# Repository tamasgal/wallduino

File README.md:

# WallDuino

Drop-in replacement board for the WallWizard remote-controlled TV wall mount
including PCB, DIY veroboard (stripboard) layouts and an open source firmware
for Arduino compatible microcontrollers.

Manual: [`WallDuino_Manual.pdf`](https://github.com/tamasgal/wallduino/blob/main/docs/WallDuino_Manual.pdf)

## Firmware

Board: Arduino Nano compatible
Dependency: [Arduino-IRRemote v4.5](https://github.com/Arduino-IRremote/Arduino-IRremote)
Code: `firmware/WallDuino`

### Changelog

#### v1.1 - 2026-01-22

- Persistent presets after reboot
- Home button support to "go home"

#### v1.0 - 2026-01-09

Initial release

## PCB

### v1.0 (Rev A) 2026-01-08

First release.

### v1.0 (Rev B) 2026-01-21

- Heat sinking of the L293D improved significantly
- R1, R2 and R3 removed
- Added an additional capacitor to smooth out the position sensor signal from the potentiometer

## DIY Veroboard

The veroboard (stripboard) is Rev A and has a different Arduino pinout, so make sure
to adjust the firmware code.

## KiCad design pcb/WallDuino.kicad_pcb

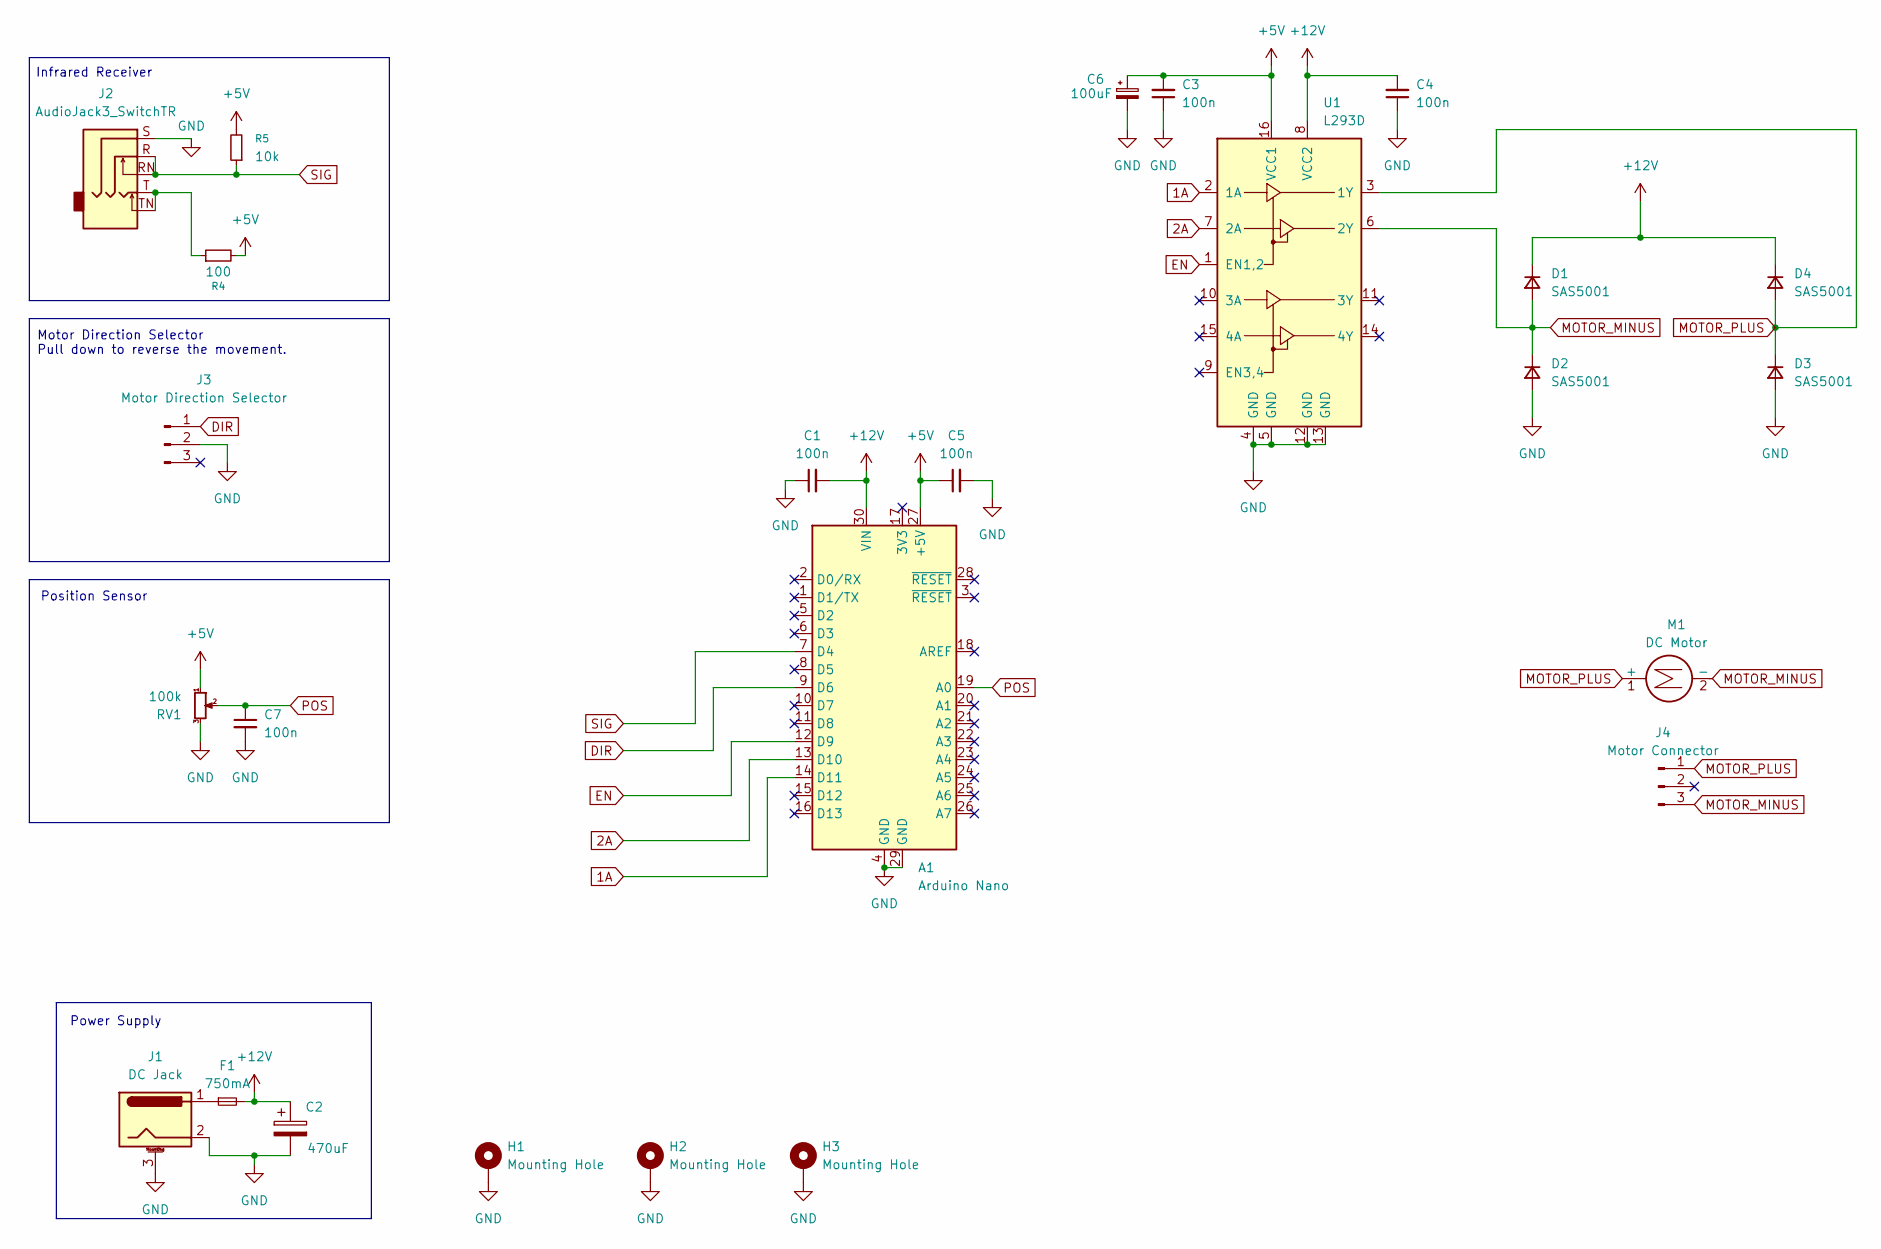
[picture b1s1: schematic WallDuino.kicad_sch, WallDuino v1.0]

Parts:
A1: Arduino Nano; Arduino_Nano
C1, C3, C4, C5, C7: 100n; C_Disc_D3.0mm_W1.6mm_P2.50mm
C2: 470uF; CP_Radial_D8.0mm_P2.50mm
C6: 100uF; CP_Radial_D5.0mm_P2.50mm
D1, D2, D3, D4: SAS5001; D_DO-34_SOD68_P7.62mm_Horizontal
F1: 750mA; R_Axial_DIN0207_L6.3mm_D2.5mm_P10.16mm_Horizontal
H1, H2, H3: Mounting Hole; MountingHole_3.5mm_Pad_Via
J1: DC Jack; BarrelJack_Horizontal
J2: AudioJack3_SwitchTR; Jack_3.5mm_CUI_SJ2-3593D-SMT_Horizontal
J3: Motor Direction Selector; PinHeader_1x03_P2.54mm_Vertical
J4: Motor Connector; JST_XH_B3B-XH-AM_1x03_P2.50mm_Vertical
M1: DC Motor
R4: 100; R_Axial_DIN0207_L6.3mm_D2.5mm_P10.16mm_Horizontal
R5: 10k; R_Axial_DIN0207_L6.3mm_D2.5mm_P10.16mm_Horizontal
RV1: 100k; JST_XH_B3B-XH-AM_1x03_P2.50mm_Vertical
U1: L293D; DIP-16_W7.62mm

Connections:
1A: A1.14 (D11), U1.2 (1A)
2A: A1.13 (D10), U1.7 (2A)
+5V: A1.27 (+5V), C3.2, C5.1, C6.1, R4.2, R5.2, RV1.1, U1.16 (VCC1)
+12V: A1.30 (VIN), C1.2, C2.1, C4.2, D1.1 (K), D4.1 (K), F1.2, U1.8 (VCC2)
DIR: A1.9 (D6), J3.1
EN: A1.12 (D9), U1.1 (EN1,2)
GND: A1.4 (GND), A1.29 (GND), C1.1, C2.2, C3.1, C4.1, C5.2, C6.2, C7.2, D2.2 (A), D3.2 (A), H1.1, H2.1, H3.1, J1.2, J1.3 (MountPin), J2.S, J3.2, RV1.3, U1.4 (GND), U1.5 (GND), U1.12 (GND), U1.13 (GND)
MOTOR_MINUS: D1.2 (A), D2.1 (K), J4.3, M1.2 (-), U1.6 (2Y)
MOTOR_PLUS: D3.1 (K), D4.2 (A), J4.1, M1.1 (+), U1.3 (1Y)
unnamed: F1.1, J1.1
unnamed: J2.T, J2.TN, R4.1
POS: A1.19 (A0), C7.1, RV1.2
SIG: A1.7 (D4), J2.R, J2.RN, R5.1

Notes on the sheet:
Infrared Receiver
Power Supply
Position Sensor
Motor Direction Selector Pull down to reverse the movement.

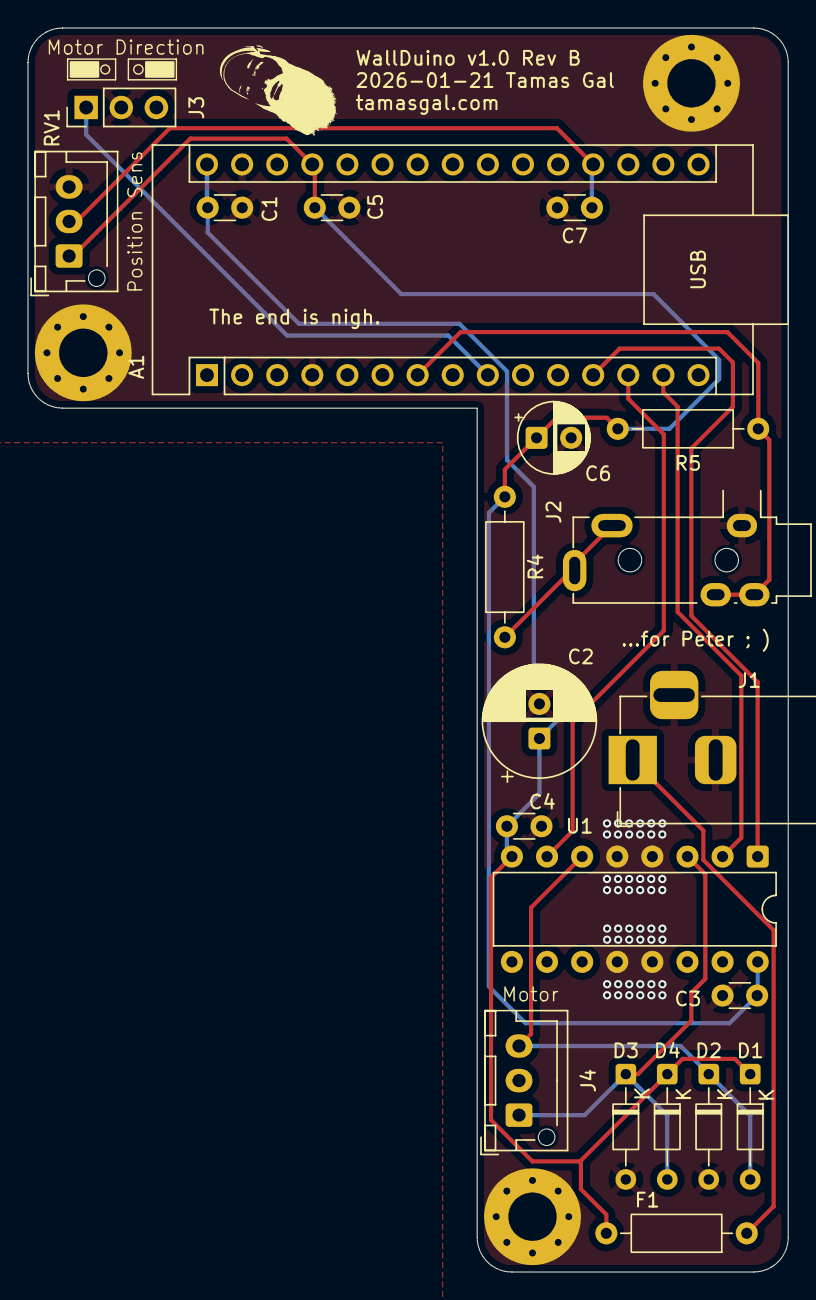
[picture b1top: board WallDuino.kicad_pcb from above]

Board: 2 copper layers, 55.0 x 90.0 mm, 24 parts (0 on the bottom side), 13 nets.

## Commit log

2026-01-10 Add README
2026-01-10 Initial commit of the firmware
2026-01-15 Add KiCAD project
2026-01-19 Update revisions
2026-01-22 Permanent preset storage and home functionality
2026-01-22 Update PCB and Schematics to v1.0 Rev B
2026-01-22 Add docs
2026-01-22 Add compiled PDF
2026-01-22 Add veroboard
2026-01-22 Update PCB preview
2026-03-02 Add some debug features
2026-03-03 Add Logitec remote and update positioning
